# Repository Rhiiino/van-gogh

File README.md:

# Van Gogh

Van Gogh is a flywheel barrel that runs as its own machine. Twin wheels take rounds from a spring magazine through a disc indexer (DIAL), one at a time. A single 6S inlet powers the whole unit. On the barrel middle, the barrel control unit (BCU) — the logic board and its printed case — listens for wireless commands on an ESP32-S3 Mini.

It is the right barrel of **Panzer**, a printed dual-barrel turret: two of these barrels on a turntable that pans and tilts them together. Van Gogh is Panzer's first barrel variant, and this repository is the second iteration, **MK II**. You can power it, assemble it, and run it on the bench with nothing else from the turret attached.

## Exploded view

## Interactive model

An interactive model of the barrel — orbit, explode, and inspect each part — is at [van-gogh.themidhunraj.com](https://van-gogh.themidhunraj.com/).

## Features + Core components

### Barrel control unit (BCU)

The barrel control unit (BCU) is the logic board and its printed case, mounted on the barrel middle. An ESP32-S3 Mini takes wireless commands and drives the rest of the barrel: the indexer and cone gearmotors, the solenoid and laser, the status LEDs, and the throttle lines to the flywheel speed controllers. Two onboard regulators step the 6S inlet down to 5 V and 6 V for those loads. Flywheel motor current stays in the power housing, on the speed controllers.

### Disc indexed Ammunition Loader (D.I.A.L)

DIAL is a five-station drum on a gearmotor. A spring magazine drops one round into each pocket as the drum indexes clockwise. A five-lobe axial face cam on the back of the drum turns with it. A spring-loaded plunger follows that cam along the bore: the rise cocks the plunger and compresses the spring, a short dwell holds it fully loaded, and a steep drop lets the spring snap the plunger forward. That stroke pushes the round at the fire station out of its pocket and into the flywheel nip. Indexing and firing are the same rotation. The cam profile sets when the shot leaves. Rinse and repeat.

### Lasenoid

A solenoid and a laser share one linkage. The solenoid stroke runs along the bore and drives an actuation rod. The other end of the rod pushes a carriage up a fixed inclined cam. The laser rides in that carriage, so the stroke raises it and brings the beam onto the bore axis.

### Cone

The muzzle cone spins on a thin-section bearing about the bore. A small gearmotor turns a pinion into a ring gear on the cone. The spin is the ready cue: a turning cone means the barrel is live, and the motion itself shows the drive is running.

### Flywheels

Two brushless motors each carry a wheel and spin in opposite directions, both contact faces moving toward the muzzle at the nip. A round pushed into that gap is gripped on both sides and accelerated down the bore. The wheels stay at speed between shots, so each plunged round meets an already-spinning pair.

### LED stick

An addressable WS2812B stick sits in the barrel middle and takes a single data line from the BCU. Each pixel can be set on its own, so the stick shows live status along its length: flywheel speed, barrel readiness, and faults.

## Photos

### Gallery

## Interface

Raw **6S** pack power (about 19–25.2 V, 22.2 V nominal) enters through an **XT90 male** in the power housing. Use a matching lead on **10 AWG** up to that connector.

The **PH ceiling / PYE connector** plate closes the power housing. Its hex socket is how the barrel mounts on Panzer when you use the full turret.

## Status

This repository documents one right barrel: the mechanical design, assembly guide, bill of materials, logic-board pin reference, and KiCad project. Printable meshes are in [models/](models/). The logic PCB was ordered as JLCPCB **Y14-2705430A** (2-layer, 56 × 92.6 mm, 1.6 mm, 1 oz, black). Sources and Gerbers: [kicad/](kicad/).

## Documentation

| File                                     | Contents                                                                                         |
| ---------------------------------------- | ------------------------------------------------------------------------------------------------ |
| [bom.md](bom.md)                         | Everything for one barrel — printed parts, fasteners, hardware, connectors, and board components |
| [cost.md](cost.md)                       | Bought-part cost for one barrel. Printed parts excluded                                          |
| [catalog.md](catalog.md)                 | Visual index of printed parts                                                                    |
| [assembly.md](assembly.md)               | Step-by-step build                                                                               |
| [power.md](power.md)                     | Inlet, XT90 split, regulators, Molex pinout, power budget                                        |
| [board.md](board.md)                     | Logic board — every reference and pin                                                            |
| [kicad/](kicad/)                         | KiCad project and `gerber.zip` for fabrication                                                   |
| [models/](models/)                       | 3D model files for the printed parts                                                             |
| [firmware/README.md](firmware/README.md) | Component-test firmware for the ESP32-S3 Mini — flash steps and the control page |
| [LICENSE](LICENSE)                       | Creative Commons Attribution-NonCommercial 4.0                                                   |

## Safety

This barrel takes a 6S lithium pack (about 19–25.2 V) and spins two brushless flywheels. A short on the XT90 or the speed-controller leads can dump the pack. The wheels store energy while they are at speed and will grab anything that enters the nip. A visible laser is aimed along the bore; do not look into the beam or aim it at anyone. Power the barrel only while it is held or clamped, and keep a way to disconnect the pack.

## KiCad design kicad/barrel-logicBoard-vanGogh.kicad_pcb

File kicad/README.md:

# Van Gogh — Logic board (KiCad)

Right-barrel barrel control unit (BCU) PCB. Open `barrel-logicBoard-vanGogh.kicad_pro` in KiCad.

| Item       | Value                         |
| ---------- | ----------------------------- |
| Board size | 56 × 92.6 mm                  |
| Layers     | 2                             |
| Thickness  | 1.6 mm                        |
| Copper     | 1 oz                          |
| Finish     | Black soldermask (as ordered) |

## Fabrication

**[gerber.zip](gerber.zip)** is the Gerber and drill export for PCB fab. It matches the board ordered from JLCPCB as **Y14-2705430A**. Upload the zip as-is; no KiCad required to order bare boards.

## Related docs

- [board.md](../board.md) — every reference and pin
- [bom.md](../bom.md) — parts to solder on the board

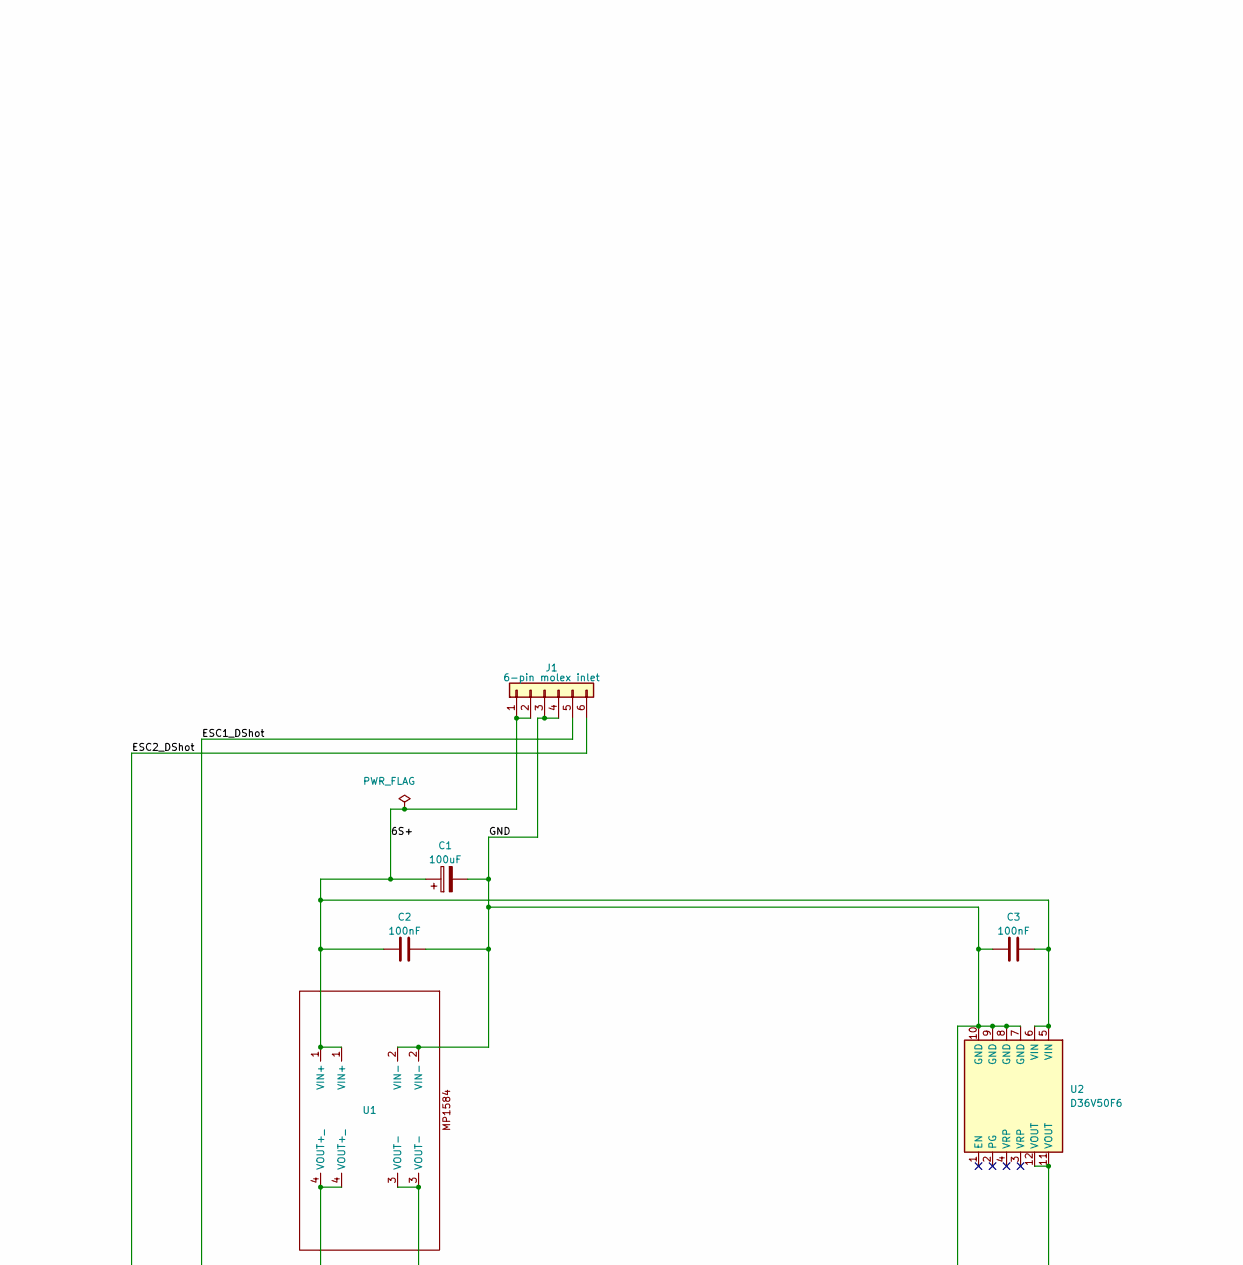
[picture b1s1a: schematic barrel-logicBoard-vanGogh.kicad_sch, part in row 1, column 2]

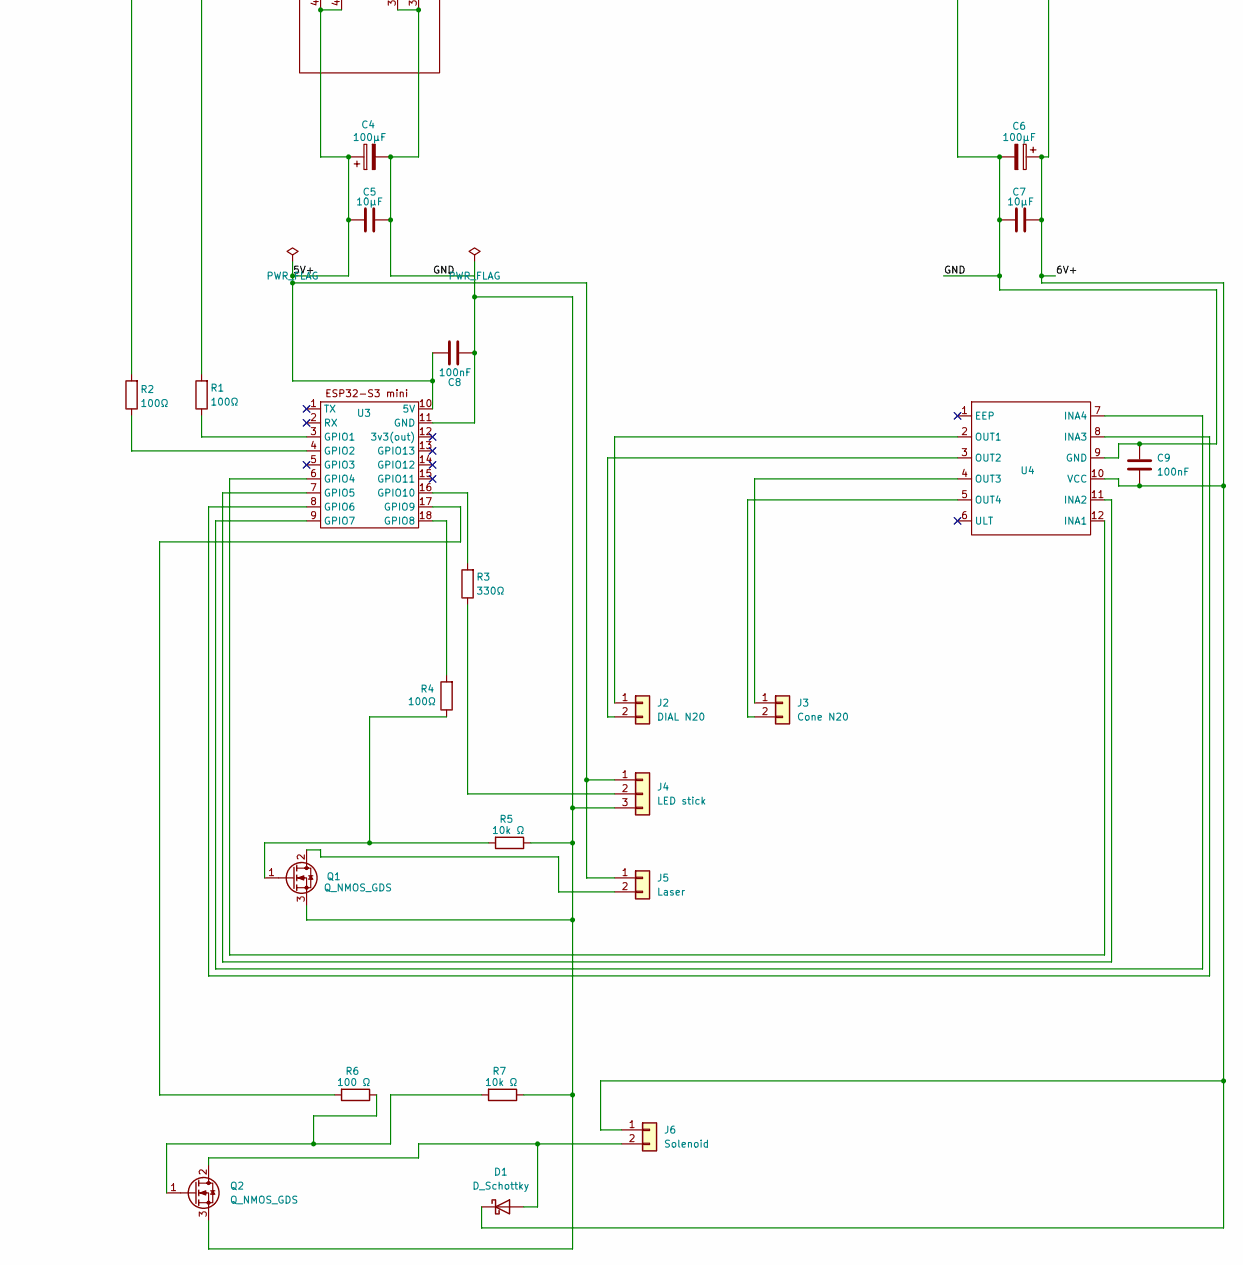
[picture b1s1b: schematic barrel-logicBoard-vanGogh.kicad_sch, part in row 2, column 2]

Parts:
C1: 100uF; CP_Radial_D8.0mm_P3.50mm
C2, C3, C8, C9: 100nF; C_1206_3216Metric_Pad1.33x1.80mm_HandSolder
C4, C6: 100µF; CP_Radial_D6.3mm_P2.50mm
C5, C7: 10µF; C_1206_3216Metric_Pad1.33x1.80mm_HandSolder
D1: D_Schottky; D_SMA_Handsoldering
J1: 6-pin molex inlet; SolderWire-0.5sqmm_1x06_P4.6mm_D0.9mm_OD2.1mm
J2: DIAL N20; JST_PH_S2B-PH-K_1x02_P2.00mm_Horizontal
J3: Cone N20; JST_PH_S2B-PH-K_1x02_P2.00mm_Horizontal
J4: LED stick; JST_PH_S3B-PH-K_1x03_P2.00mm_Horizontal
J5: Laser; JST_PH_S2B-PH-K_1x02_P2.00mm_Horizontal
J6: Solenoid; JST_PH_S2B-PH-K_1x02_P2.00mm_Horizontal
Q1, Q2: Q_NMOS_GDS; TO-252-2
R1, R2, R4: 100Ω; R_1206_3216Metric_Pad1.30x1.75mm_HandSolder
R3: 330Ω; R_1206_3216Metric_Pad1.30x1.75mm_HandSolder
R5, R7: 10k Ω; R_1206_3216Metric_Pad1.30x1.75mm_HandSolder
R6: 100 Ω; R_1206_3216Metric_Pad1.30x1.75mm_HandSolder
U1: MP1584
U2: D36V50F6
U3: ESP32_s3_supermini
U4: DRV8833

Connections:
/5V+: C4.1, C5.1, C8.1, J4.1, J5.1, U1.4 (VOUT+_), U3.10 (5V)
/6S+: C1.1, C2.1, C3.2, J1.1, J1.2, U1.1 (VIN+), U2.5 (VIN), U2.6 (VIN)
/6V+: C6.1, C7.2, C9.2, D1.1 (K), J6.1, U2.11 (VOUT), U2.12 (VOUT), U4.10 (VCC)
/ESC1_DShot: J1.5, R1.2
/ESC2_DShot: J1.6, R2.2
/GND: C1.2, C2.2, C3.1, C4.2, C5.2, C6.2, C7.1, C8.2, C9.1, J1.3, J1.4, J4.3, Q1.3 (S), Q2.3 (S), R5.1, R7.1, U1.2 (VIN-), U1.3 (VOUT-), U2.7 (GND), U2.8 (GND), U2.9 (GND), U2.10 (GND), U3.11 (GND), U4.9 (GND)
unnamed: D1.2 (A), J6.2, Q2.2 (D)
unnamed: J2.1, U4.2 (OUT1)
unnamed: J2.2, U4.3 (OUT2)
unnamed: J3.1, U4.4 (OUT3)
unnamed: J3.2, U4.5 (OUT4)
unnamed: J4.2, R3.1
unnamed: J5.2, Q1.2 (D)
unnamed: Q1.1 (G), R4.1, R5.2
unnamed: Q2.1 (G), R6.1, R7.2
unnamed: R1.1, U3.3 (GPIO1)
unnamed: R2.1, U3.4 (GPIO2)
unnamed: U3.6 (GPIO4), U4.12 (INA1)
unnamed: U3.7 (GPIO5), U4.11 (INA2)
unnamed: U3.8 (GPIO6), U4.8 (INA3)
unnamed: U3.9 (GPIO7), U4.7 (INA4)
unnamed: R4.2, U3.18 (GPIO8)
unnamed: R6.2, U3.17 (GPIO9)
unnamed: R3.2, U3.16 (GPIO10)

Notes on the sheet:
Hey Chris.

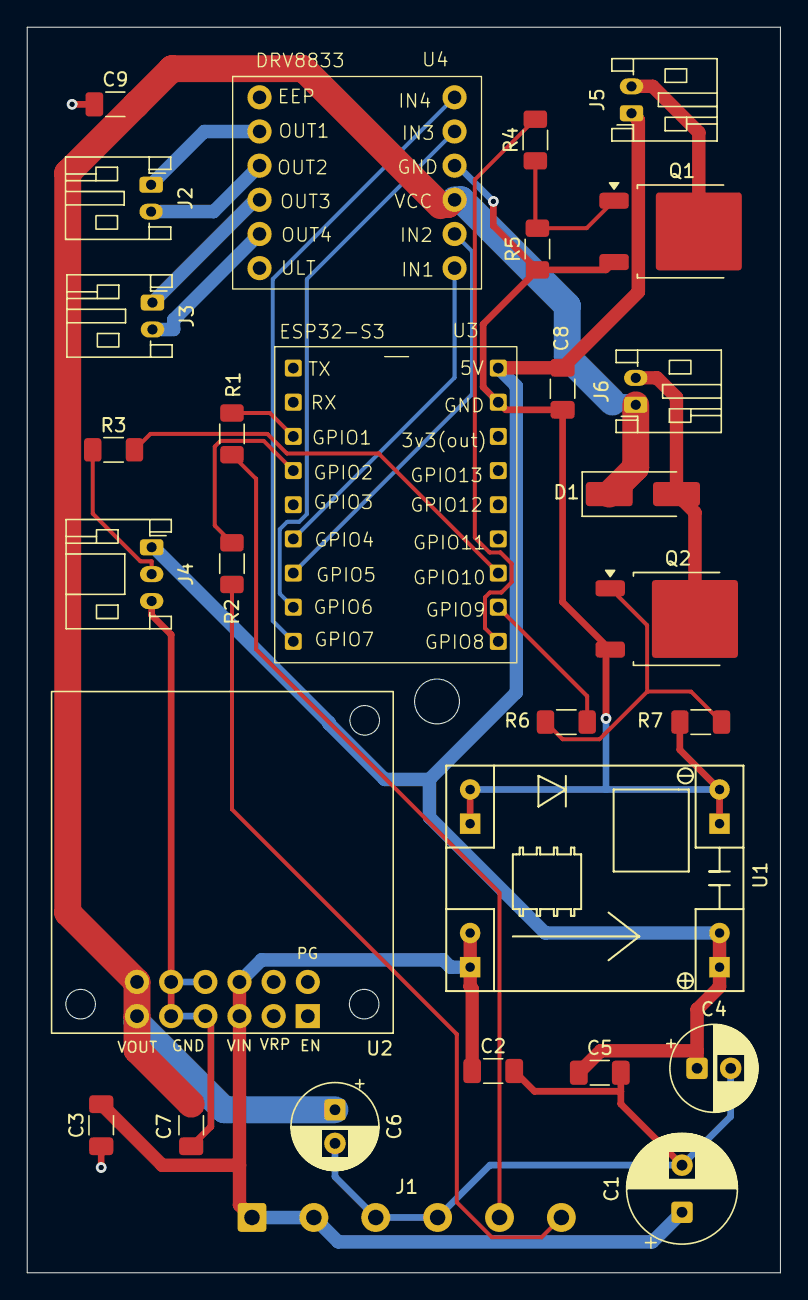
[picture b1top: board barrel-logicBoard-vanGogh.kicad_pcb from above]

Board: 2 copper layers, 56.0 x 92.6 mm, 29 parts (0 on the bottom side), 24 nets.

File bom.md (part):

# Van Gogh — BOM

Everything required to build **one** barrel. Quantities are per barrel. Hub: [README.md](README.md).

Part numbers and board placement: [board.md](board.md). Bought-part cost: [cost.md](cost.md).

---

## Printed

One row is one printed part. Qty is per barrel. **Specifications** is material and slicer settings when recorded. Images: [catalog.md](catalog.md).


| Part                       | Qty | Specifications    |
| -------------------------- | --- | ----------------- |
| actuation rod              | 1   | 100% infill, PETG |
| ammo guide                 | 1   | 100% infill, PETG |
| barrel base L panel        | 1   | 100% infill, PETG |
| barrel base R panel        | 1   | 100% infill, PETG |
| barrel middle              | 1   |                   |
| BCU cover                  | 1   |                   |
| cone                       | 1   | 100% infill, PETG |
| drum cam                   | 1   |                   |
| drum main                  | 1   |                   |
| drum motor shaft           | 1   | 100% infill, PETG |
| ESC casing                 | 2   | 100% infill, PETG |
| flywheel                   | 2   |                   |
| flywheel base              | 1   |                   |
| flywheel carriage          | 1   |                   |
| lasenoid base              | 1   |                   |
| laser carriage             | 1   |                   |
| led & cone n20 motor panel | 1   |                   |
| magazine lid               | 1   |                   |
| magazine main              | 1   |                   |
| magazine mount             | 1   |                   |
| magazine pusher            | 1   | 0.08mm quality, 100% infill, PETG |
| module - name plate        | 1   |                   |
| name & lasenoid panel      | 1   |                   |
| PH ceiling / PYE connector | 1   |                   |
| pinion gear                | 1   | 100% infill, PETG |
| plunger                    | 1   | 100% infill, PETG |
| plunger mount              | 1   | 100% infill, PETG |
| power housing              | 1   | 100% infill, PETG |
| solenoid / rod pin         | 1   |                   |


## Fasteners

A magnet join is one magnet on each part, opposite poles facing, so the two parts hold together.

### Magnets

One row is one join. **Qty each** is the magnet count on that part and on its counterpart.


| Join                                        | Part                       | Counterpart       | Qty each | Total |
| ------------------------------------------- | -------------------------- | ----------------- | -------- | ----- |
| BCU cover to barrel middle                  | BCU cover                  | Barrel middle     | 2        | 4     |
| Name & lasenoid panel to barrel middle      | name & lasenoid panel      | Barrel middle     | 2        | 4     |
| LED & cone N20 motor panel to barrel middle | led & cone n20 motor panel | Barrel middle     | 2        | 4     |
| Barrel base L panel to flywheel carriage    | barrel base L panel        | flywheel carriage | 1        | 2     |
| Barrel base R panel to flywheel carriage    | barrel base R panel        | flywheel carriage | 1        | 2     |


### M3 bolts and heat-set inserts

One row is one bolt path. Every bolt is an M3. **Through** is the part under the bolt head, then any parts the bolt passes, in that order. **Insert in** is the last part, the one with the heat-set insert. **Length** is the bolt length. **Qty** is the number of bolts on that path. Each bolt has one insert, except the flywheel-motor bolts, which thread into the motor.


| Join                                                 | Through                       | Insert in         | Length | Qty |
| ---------------------------------------------------- | ----------------------------- | ----------------- | ------ | --- |
| Magazine mount to barrel middle                      | magazine mount                | barrel middle     | 6 mm   | 2   |
| Magazine mount to flywheel carriage                  | magazine mount                | flywheel carriage | 6 mm   | 1   |
| Logic board to barrel middle                         | logic board                   | barrel middle     | 6 mm   | 1   |
| Plunger mount to flywheel base                       | plunger mount                 | flywheel base     | 35 mm  | 1   |
| Ammo guide to flywheel base                          | flywheel base                 | ammo guide        | 12 mm  | 1   |
| Flywheel carriage to power housing and flywheel base | power housing → flywheel base | flywheel carriage | 12 mm  | 2   |
| Power housing to flywheel base                       | power housing                 | flywheel base     | 6 mm   | 1   |
| Flywheel motor to flywheel base                      | flywheel base                 | —                 | 6 mm   | 4   |
| PH ceiling / PYE connector to power housing          | PH ceiling / PYE connector    | power housing     | 8 mm   | 3   |


The flywheel-motor path is four bolts, two per motor. Each bolt passes through the **flywheel base** and threads into the **Flywheel motor**. There is no heat-set insert on that path.

## Mechanical


| Part           | Qty | Spec                           | Listing |
| -------------- | --- | ------------------------------ | ------- |
| Ring bearing   | 1   | uxcell 6706-2RS, 30 × 37 × 4 mm | [Amazon](https://www.amazon.com/dp/B082PSDLTS) |
| Solenoid       | 1   | MEETOOT SM0537, 6 V / 1.5 A    | — |
| Flywheel motor | 2   | iFlight XING-E Pro 2207 1800KV | [Amazon](https://www.amazon.com/iFlight-1800KV-Brushless-Racing-Quadc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 |
| LED stick      | 1   | WS2812B                        | — |
| ESC            | 2   | HNYYZL/LANRC 45A BLHeli_S      | [Amazon](https://www.amazon.com/HNYYZL-Brushless-Electronic-Controlle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 |
| N20 motor      | 2   | DWEII                          | — |
| Plunger spring | 1   | 0.5 × 6 × 30 mm (Glarks kit)   | [Amazon](https://www.amazon.com/dp/B09PY68K9C) |


The ring bearing spins the cone. The plunger spring is the 30 mm piece from the Glarks assortment.

## Connectors and wire


| Part                     | Qty | Where         | Listing |
| ------------------------ | --- | ------------- | ------- |
| Micro-Fit 3.0 1×6 female | 1   | Power housing | [Amazon](https://www.amazon.com/dp/B0CL9MG9PY) |
| Micro-Fit 3.0 1×6 male   | 1   | Barrel middle | same kit |
| XT90 male                | 1   | Power housing | — |


## Logic board

The PCB and the parts soldered on it. Qty is per barrel. Silkscreen refs and pins: [board.md](board.md). Bare board: order [kicad/gerber.zip](kicad/gerber.zip). Design source: [kicad/](kicad/).


| Part                             | Qty | Spec                                                            |
| -------------------------------- | --- | --------------------------------------------------------------- |
| Van Gogh logic PCB               | 1   | 56 × 92.6 mm, 2-layer, 1.6 mm, 1 oz. Fab: [gerber.zip](kicad/gerber.zip) |
| ESP32-S3 Mini                    | 1   | Aideepen. U3. [Amazon](https://www.amazon.com/dp/B0H3PJD525) |
| MP1584EN                         | 1   | +5 V buck. U1. [Amazon](https://www.amazon.com/dp/B01MQGMOKI) |
| Pololu D36V50F6                  | 1   | +6 V buck, #4092. U2. [Pololu](https://www.pololu.com/product/4092) |
| DRV8833 module                   | 1   | WWZMDiB. Both N20s. U4. [Amazon](https://www.amazon.com/dp/B0DB8CX8LK) |
| 100 µF 50 V electrolytic         | 1   | 8 × 12 mm. C1, 6S inlet. [Amazon](https://www.amazon.com/dp/B0CMQ8XQ4N) |
| 100 µF 16 V electrolytic         | 2   | C4 on +5 V, C6 on +6 V. [Amazon](https://www.amazon.com/dp/B07PBQXQNQ) |
| 100 nF 50 V ceramic              | 4   | 1206. C2, C3, C8, C9. [Amazon](https://www.amazon.com/dp/B0F5Q8V6BH) |
| 10 µF 50 V ceramic               | 2   | 1206. C5 on +5 V, C7 on +6 V. same kit |
| 100 Ω                            | 4   | 1206. R1, R2 DShot; R4, R6 gate series. [Amazon](https://www.amazon.com/dp/B08RYMYWG9) |
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
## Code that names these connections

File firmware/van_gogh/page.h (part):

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    <section class="panel">
      <p class="kicker">INDEXER</p>
      <h2>DIAL</h2>
      <p class="note">GPIO4 and GPIO5 drive the drum motor on J2. Any run is full 6 V for the time you set. Reverse the direction if the drum turns the wrong way. Coast releases the motor. Brake holds it.</p>
      <div class="fields">
        <label><span>DIRECTION</span>
          <select id="dialDir">
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    <section class="panel">
      <p class="kicker">MUZZLE</p>
      <h2>Cone</h2>
      <p class="note">GPIO6 and GPIO7 drive the cone motor on J3. Same full-voltage run as the indexer. A turning cone is the ready cue.</p>
      <div class="fields">
        <label><span>DIRECTION</span>
          <select id="coneDir">
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    <section class="panel">
      <p class="kicker">LASENOID</p>
      <h2>Laser</h2>
      <p class="note">GPIO8 switches the laser on J5. Do not look into the beam or aim it at anyone. Pulse turns it off by itself. Stay on holds until Laser off or E-stop.</p>
      <label><span>PULSE MS</span><input id="laserMs" type="number" min="50" max="60000" value="500"></label>
      <div class="row">
        <button class="primary" id="laserPulse" type="button">Pulse</button>
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    <section class="panel">
      <p class="kicker">LASENOID</p>
      <h2>Solenoid</h2>
      <p class="note">GPIO9 pulses the solenoid on J6. It always turns off by itself. The longest pulse is 8 seconds. E-stop ends one early.</p>
      <label><span>PULSE MS</span><input id="solMs" type="number" min="50" max="8000" value="300"></label>
      <div class="row">
        <button class="warn" id="solFire" type="button">Pulse solenoid</button>
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  <section class="panel">
    <p class="kicker">BARREL MIDDLE</p>
    <h2>LED stick</h2>
    <p class="note">GPIO10 is the data line on J4. The stick on this barrel is 12 pixels. Light one pixel to walk the chain. A dark tail means the data stops at the last lit pixel.</p>
    <div class="fields">
      <label><span>PIXELS</span><input id="ledCount" type="number" min="1" max="64" value="12"></label>
      <label><span>BRIGHTNESS %</span><input id="ledBright" type="number" min="0" max="100" value="40"></label>
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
